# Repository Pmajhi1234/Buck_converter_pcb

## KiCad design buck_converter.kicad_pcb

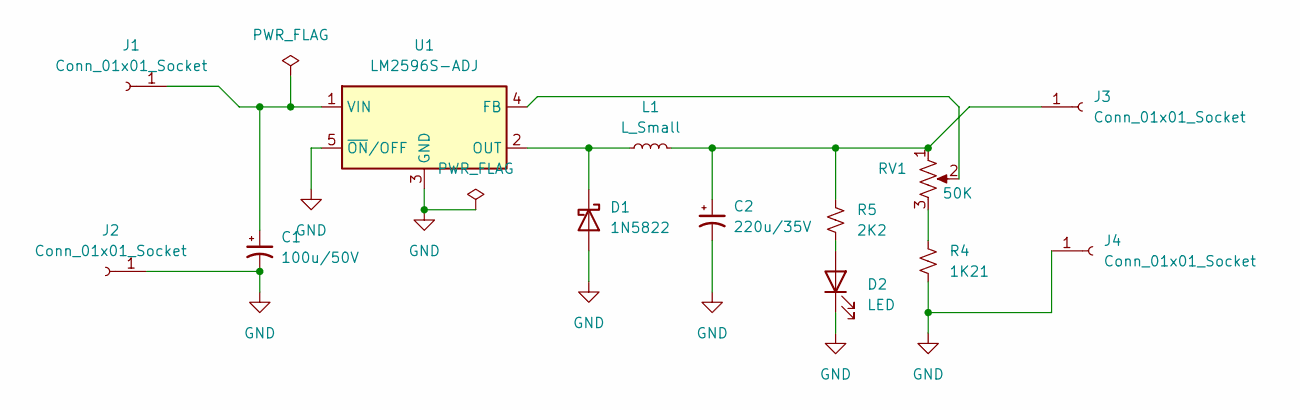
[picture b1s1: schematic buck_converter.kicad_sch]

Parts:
C1: 100u/50V; CP_Elec_6.3x5.3
C2: 220u/35V; CP_Elec_6.3x5.3
D1: 1N5822; D_2010_5025Metric
D2: LED; LED_1206_3216Metric
J1, J2, J3, J4: Conn_01x01_Socket; SolderWire-0.5sqmm_1x01_D0.9mm_OD2.1mm
L1: L_Small; L_Chilisin_BMRA00040415
R4: 1K21; R_0402_1005Metric
R5: 2K2; R_1206_3216Metric
RV1: 50K; Potentiometer_Bourns_3296Y_Vertical
U1: LM2596S-ADJ; TO-263-5_TabPin3

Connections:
GND: C1.2, C2.2, D1.2 (A), D2.1 (K), J2.1, J4.1, R4.2, U1.3 (GND), U1.5 (~ON/OFF)
unnamed: D1.1 (K), L1.1, U1.2 (OUT)
unnamed: D2.2 (A), R5.2
unnamed: C1.1, J1.1, U1.1 (VIN)
unnamed: R4.1, RV1.3
unnamed: RV1.2, U1.4 (FB)
Vout: C2.1, J3.1, L1.2, R5.1, RV1.1

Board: 2 copper layers, 13 parts (0 on the bottom side), 7 nets, no tracks yet.
